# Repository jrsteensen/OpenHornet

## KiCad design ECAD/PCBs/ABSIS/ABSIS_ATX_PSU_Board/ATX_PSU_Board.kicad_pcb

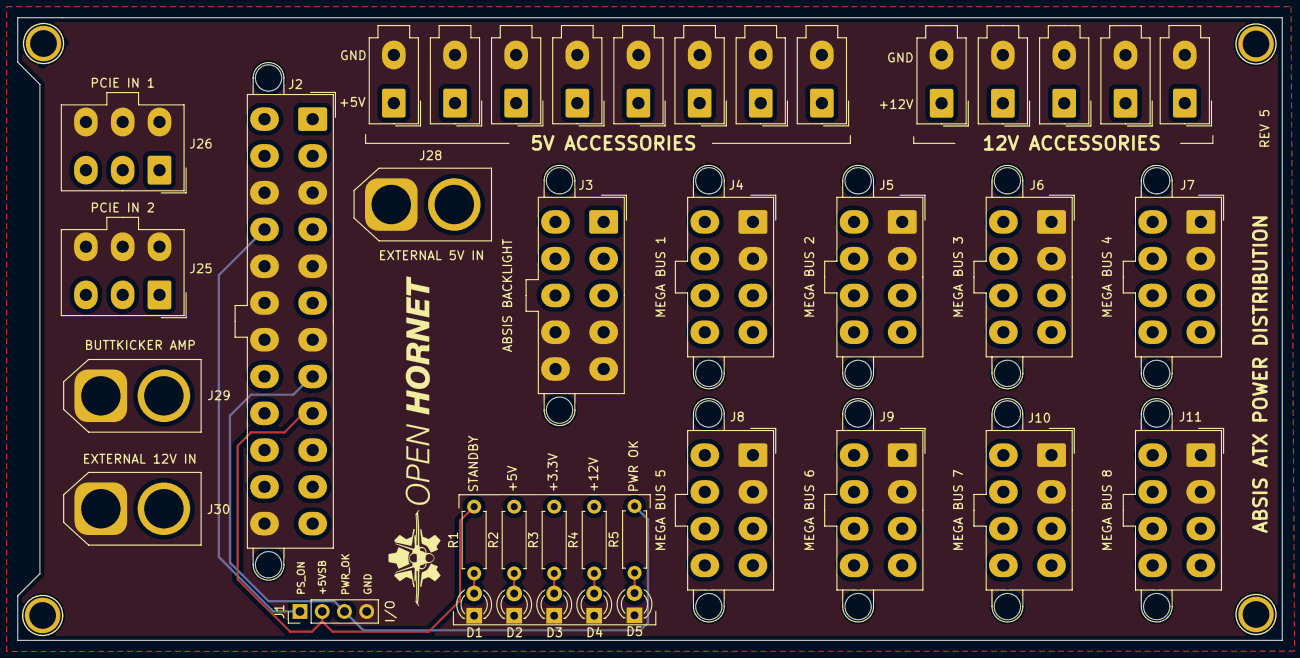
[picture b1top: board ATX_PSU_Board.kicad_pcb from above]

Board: 4 copper layers, 144.4 x 71.1 mm, 43 parts (0 on the bottom side), 12 nets.

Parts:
D1: Blue LED; LED_D3.0mm
D2, D3, D4, D5: Green LED; LED_D3.0mm
H1, H2, H3, H4: MountingHole; Arduino_1pin
J1: I/O; PinHeader_1x04_P2.54mm_Vertical
J2: ATX-24; Molex_Mini-Fit_Jr_5566-24A2_2x12_P4.20mm_Vertical
J3: ABSIS BACKLIGHT; Molex_Mini-Fit_Jr_5566-10A2_2x05_P4.20mm_Vertical
J4: MEGA BUS 1; Molex_Mini-Fit_Jr_5566-08A2_2x04_P4.20mm_Vertical
J5: MEGA BUS 2; Molex_Mini-Fit_Jr_5566-08A2_2x04_P4.20mm_Vertical
J6: MEGA BUS 3; Molex_Mini-Fit_Jr_5566-08A2_2x04_P4.20mm_Vertical
J7: MEGA BUS 4; Molex_Mini-Fit_Jr_5566-08A2_2x04_P4.20mm_Vertical
J8: MEGA BUS 5; Molex_Mini-Fit_Jr_5566-08A2_2x04_P4.20mm_Vertical
J9: MEGA BUS 6; Molex_Mini-Fit_Jr_5566-08A2_2x04_P4.20mm_Vertical
J10: MEGA BUS 7; Molex_Mini-Fit_Jr_5566-08A2_2x04_P4.20mm_Vertical
J11: MEGA BUS 8; Molex_Mini-Fit_Jr_5566-08A2_2x04_P4.20mm_Vertical
J12: 5V Accessory 1; Molex_Mini-Fit_Jr_5566-02A_2x01_P4.20mm_Vertical
J13: 5V Accessory 2; Molex_Mini-Fit_Jr_5566-02A_2x01_P4.20mm_Vertical
J14: 5V Accessory 3; Molex_Mini-Fit_Jr_5566-02A_2x01_P4.20mm_Vertical
J15: 5V Accessory 4; Molex_Mini-Fit_Jr_5566-02A_2x01_P4.20mm_Vertical
J16: 5V Accessory 5; Molex_Mini-Fit_Jr_5566-02A_2x01_P4.20mm_Vertical
J17: 5V Accessory 6; Molex_Mini-Fit_Jr_5566-02A_2x01_P4.20mm_Vertical
J18: 5V Accessory 7; Molex_Mini-Fit_Jr_5566-02A_2x01_P4.20mm_Vertical
J19: 5V Accessory 8; Molex_Mini-Fit_Jr_5566-02A_2x01_P4.20mm_Vertical
J20: 12V Accessory 1; Molex_Mini-Fit_Jr_5566-02A_2x01_P4.20mm_Vertical
J21: 12V Accessory 2; Molex_Mini-Fit_Jr_5566-02A_2x01_P4.20mm_Vertical
J22: 12V Accessory 3; Molex_Mini-Fit_Jr_5566-02A_2x01_P4.20mm_Vertical
J23: 12V Accessory 4; Molex_Mini-Fit_Jr_5566-02A_2x01_P4.20mm_Vertical
J24: 12V Accessory 5; Molex_Mini-Fit_Jr_5566-02A_2x01_P4.20mm_Vertical
J25: PCIE IN 2; Molex_Mini-Fit_Jr_5566-06A_2x03_P4.20mm_Vertical
J26: PCIE IN 1; Molex_Mini-Fit_Jr_5566-06A_2x03_P4.20mm_Vertical
J28: EXTERNAL 5V IN; AMASS_XT60-M_1x02_P7.20mm_Vertical
J29: BUTTKICKER AMP; AMASS_XT60-F_1x02_P7.20mm_Vertical
J30: EXTERNAL 12V IN; AMASS_XT60-M_1x02_P7.20mm_Vertical
R1, R2, R5: 150; R_Axial_DIN0207_L6.3mm_D2.5mm_P7.62mm_Horizontal
R3: 56; R_Axial_DIN0207_L6.3mm_D2.5mm_P7.62mm_Horizontal
R4: 560; R_Axial_DIN0207_L6.3mm_D2.5mm_P7.62mm_Horizontal

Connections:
/+3.3V_SUPPLY: J2.1, J2.2, J2.12, J2.13, J4.5, J5.5, J6.5, J7.5, J8.5, J9.5, J10.5, J11.5, R3.2
/+5VSB_SUPPLY: J1.2, J2.9, R1.2
/+5V_SUPPLY: J2.4, J2.6, J2.21, J2.22, J2.23, J3.1, J3.2, J3.3, J3.6, J3.7, J4.6, J4.7, J5.6, J5.7, J6.6, J6.7, J7.6, J7.7, J8.6, J8.7, J9.6, J9.7, J10.6, J10.7, J11.6, J11.7, J12.1, J13.1, J14.1, J15.1, J16.1, J17.1, J18.1, J19.1, J28.2, R2.2
/+12V_SUPPLY: J2.10, J2.11, J3.8, J4.3, J4.4, J4.8, J5.3, J5.4, J5.8, J6.3, J6.4, J6.8, J7.3, J7.4, J7.8, J8.3, J8.4, J8.8, J9.3, J9.4, J9.8, J10.3, J10.4, J10.8, J11.3, J11.4, J11.8, J20.1, J21.1, J22.1, J23.1, J24.1, J25.1, J25.2, J25.3, J26.1, J26.2, J26.3, J29.2, J30.2, R4.2
/PS_ON: J1.1, J2.16
/PWR_OK: J1.3, J2.8, R5.2
GND: D1.1, D2.1, D3.1, D4.1, D5.1, J1.4, J2.3, J2.5, J2.7, J2.15, J2.17, J2.18, J2.19, J2.24, J3.4, J3.5, J3.9, J3.10, J4.1, J4.2, J5.1, J5.2, J6.1, J6.2, J7.1, J7.2, J8.1, J8.2, J9.1, J9.2, J10.1, J10.2, J11.1, J11.2, J12.2, J13.2, J14.2, J15.2, J16.2, J17.2, J18.2, J19.2, J20.2, J21.2, J22.2, J23.2, J24.2, J25.4, J25.5, J25.6, J26.4, J26.5, J26.6, J28.1, J29.1, J30.1
unnamed: D1.2, R1.1
unnamed: D2.2, R2.1
unnamed: D3.2, R3.1
unnamed: D4.2, R4.1
unnamed: D5.2, R5.1

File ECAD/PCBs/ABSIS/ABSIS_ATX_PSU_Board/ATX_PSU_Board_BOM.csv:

"Id";"Designator";"Package";"Quantity";"Designation";"Supplier and ref";
1;"R4";"R_0603_1608Metric_Pad0.98x0.95mm_HandSolder";1;"560";;;
2;"R3";"R_0603_1608Metric_Pad0.98x0.95mm_HandSolder";1;"56";;;
3;"R2,R1";"R_0603_1608Metric_Pad0.98x0.95mm_HandSolder";2;"150";;;
4;"D4,D3,D2,D1";"LED_0603_1608Metric_Pad1.05x0.95mm_HandSolder";4;"Green LED";;;
5;"J1";"PinHeader_1x02_P2.54mm_Vertical";1;"Power Swtich";;;
6;"G***,G***";"CC-BY-NC-SA-Small";2;"LOGO";;;
7;"G***";"OH_LOGO_75.4mm_11.9mm";1;"LOGO";;;
8;"J5,J10,J9,J8,J7,J6,J4";"Molex_Mini-Fit_Jr_5566-08A2_2x04_P4.20mm_Vertical";7;"MEGA BUS POWER";;;
9;"G***";"OH_LOGO_37.7mm_5.9mm";1;"LOGO";;;
10;"H4,H3,H2,H1";"Arduino_1pin";4;"MountingHole";;;
11;"J3";"Molex_Mini-Fit_Jr_5566-10A2_2x05_P4.20mm_Vertical";1;"ABSIS BACKLIGHT PWR";;;
12;"J2";"Molex_Mini-Fit_Jr_5566-24A2_2x12_P4.20mm_Vertical";1;"ATX-24";;;

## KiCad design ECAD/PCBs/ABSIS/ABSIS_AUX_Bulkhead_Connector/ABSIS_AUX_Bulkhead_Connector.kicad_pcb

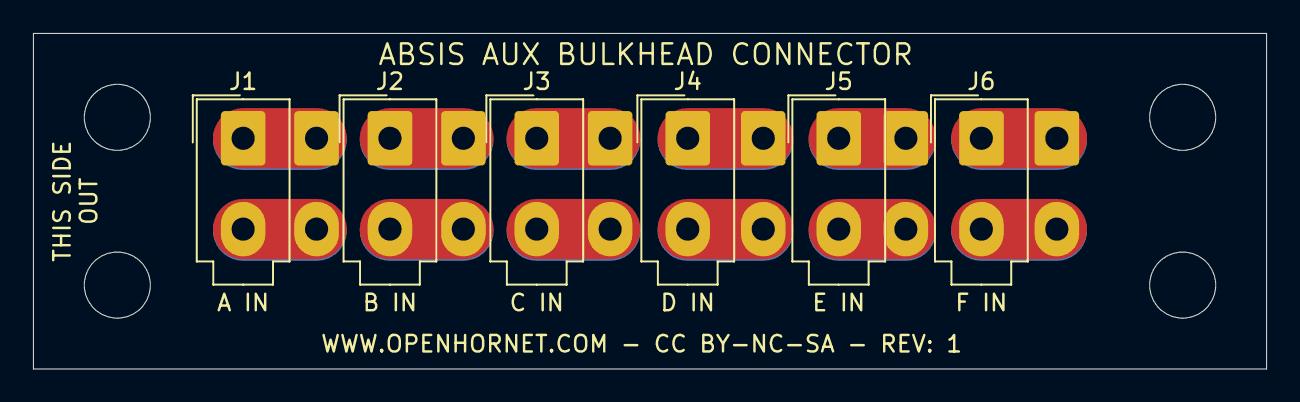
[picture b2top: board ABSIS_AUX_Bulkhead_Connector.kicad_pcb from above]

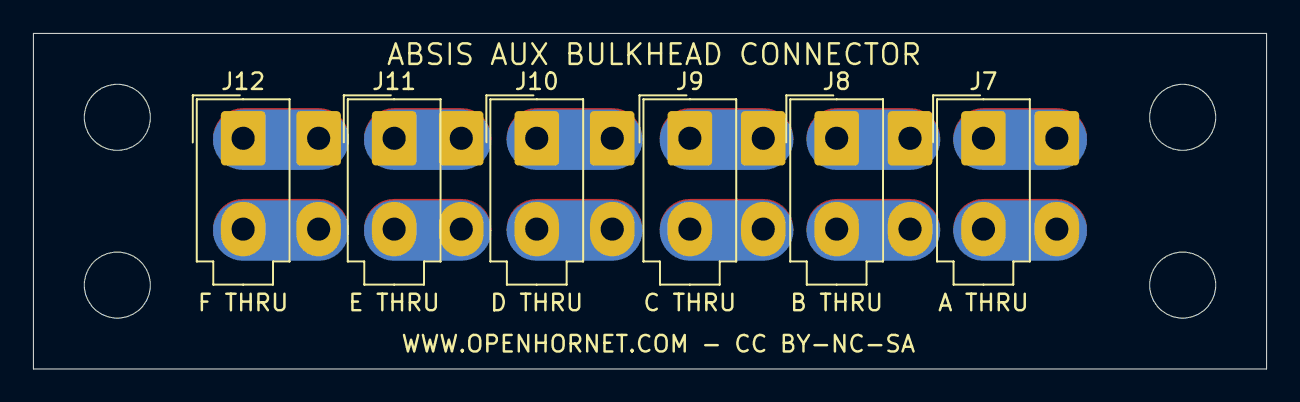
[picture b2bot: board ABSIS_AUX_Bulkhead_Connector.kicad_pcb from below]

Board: 2 copper layers, 74.7 x 20.3 mm, 16 parts (6 on the bottom side), 12 nets.

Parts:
H1, H2, H3, H4: MH; MountingHole_4mm
J1: A IN; Molex_Mini-Fit_Jr_5566-02A_2x01_P4.20mm_Vertical
J2: B IN; Molex_Mini-Fit_Jr_5566-02A_2x01_P4.20mm_Vertical
J3: C IN; Molex_Mini-Fit_Jr_5566-02A_2x01_P4.20mm_Vertical
J4: D IN; Molex_Mini-Fit_Jr_5566-02A_2x01_P4.20mm_Vertical
J5: E IN; Molex_Mini-Fit_Jr_5566-02A_2x01_P4.20mm_Vertical
J6: F IN; Molex_Mini-Fit_Jr_5566-02A_2x01_P4.20mm_Vertical
J7: A THRU; Molex_Mini-Fit_Jr_5566-02A_2x01_P4.20mm_Vertical
J8: B THRU; Molex_Mini-Fit_Jr_5566-02A_2x01_P4.20mm_Vertical
J9: C THRU; Molex_Mini-Fit_Jr_5566-02A_2x01_P4.20mm_Vertical
J10: D THRU; Molex_Mini-Fit_Jr_5566-02A_2x01_P4.20mm_Vertical
J11: E THRU; Molex_Mini-Fit_Jr_5566-02A_2x01_P4.20mm_Vertical
J12: F THRU; Molex_Mini-Fit_Jr_5566-02A_2x01_P4.20mm_Vertical

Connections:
/A1: J1.1, J7.1
/A2: J1.2, J7.2
/B1: J2.1, J8.1
/B2: J2.2, J8.2
/C1: J3.1, J9.1
/C2: J3.2, J9.2
/D1: J4.1, J10.1
/D2: J4.2, J10.2
/E1: J5.1, J11.1
/E2: J5.2, J11.2
/F1: J6.1, J12.1
/F2: J6.2, J12.2

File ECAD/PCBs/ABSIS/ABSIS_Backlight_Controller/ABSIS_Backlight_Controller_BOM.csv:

Reference, Quantity, Value, Footprint, Datasheet, PN
J1 ,1,"Molex Mini-Fit Jr, Header, 2x5",Connector_Molex:Molex_Mini-Fit_Jr_5566-10A2_2x05_P4.20mm_Vertical,https://www.molex.com/pdm_docs/sd/039299103_sd.pdf,39299103
J2 J3 J4 J5 J6 J7 J8 J9 J10 J11 J12 J13,12,"Molex Mini-Fit Jr, Header, 2x2",Connector_Molex:Molex_Mini-Fit_Jr_5566-04A_2x02_P4.20mm_Vertical,https://www.molex.com/pdm_docs/sd/039281043_sd.pdf,39281043
J14 ,1,"Pin Header, 2.54mm, 2x6",Connector_PinHeader_2.54mm:PinHeader_2x06_P2.54mm_Vertical,~,
J15 ,1,"Pin Header, 2.54mm, 2x8",Connector_PinHeader_2.54mm:PinHeader_2x08_P2.54mm_Vertical,~,
P1 ,1,Digital,Connector_PinHeader_2.54mm:PinHeader_2x18_P2.54mm_Vertical,~,
P2 P3 P4 P6 P7,5,"Pin Header, 2.54mm, 1x8",Connector_PinHeader_2.54mm:PinHeader_1x08_P2.54mm_Vertical,~,
P5 ,1,PWM,Connector_PinHeader_2.54mm:PinHeader_1x10_P2.54mm_Vertical,~,

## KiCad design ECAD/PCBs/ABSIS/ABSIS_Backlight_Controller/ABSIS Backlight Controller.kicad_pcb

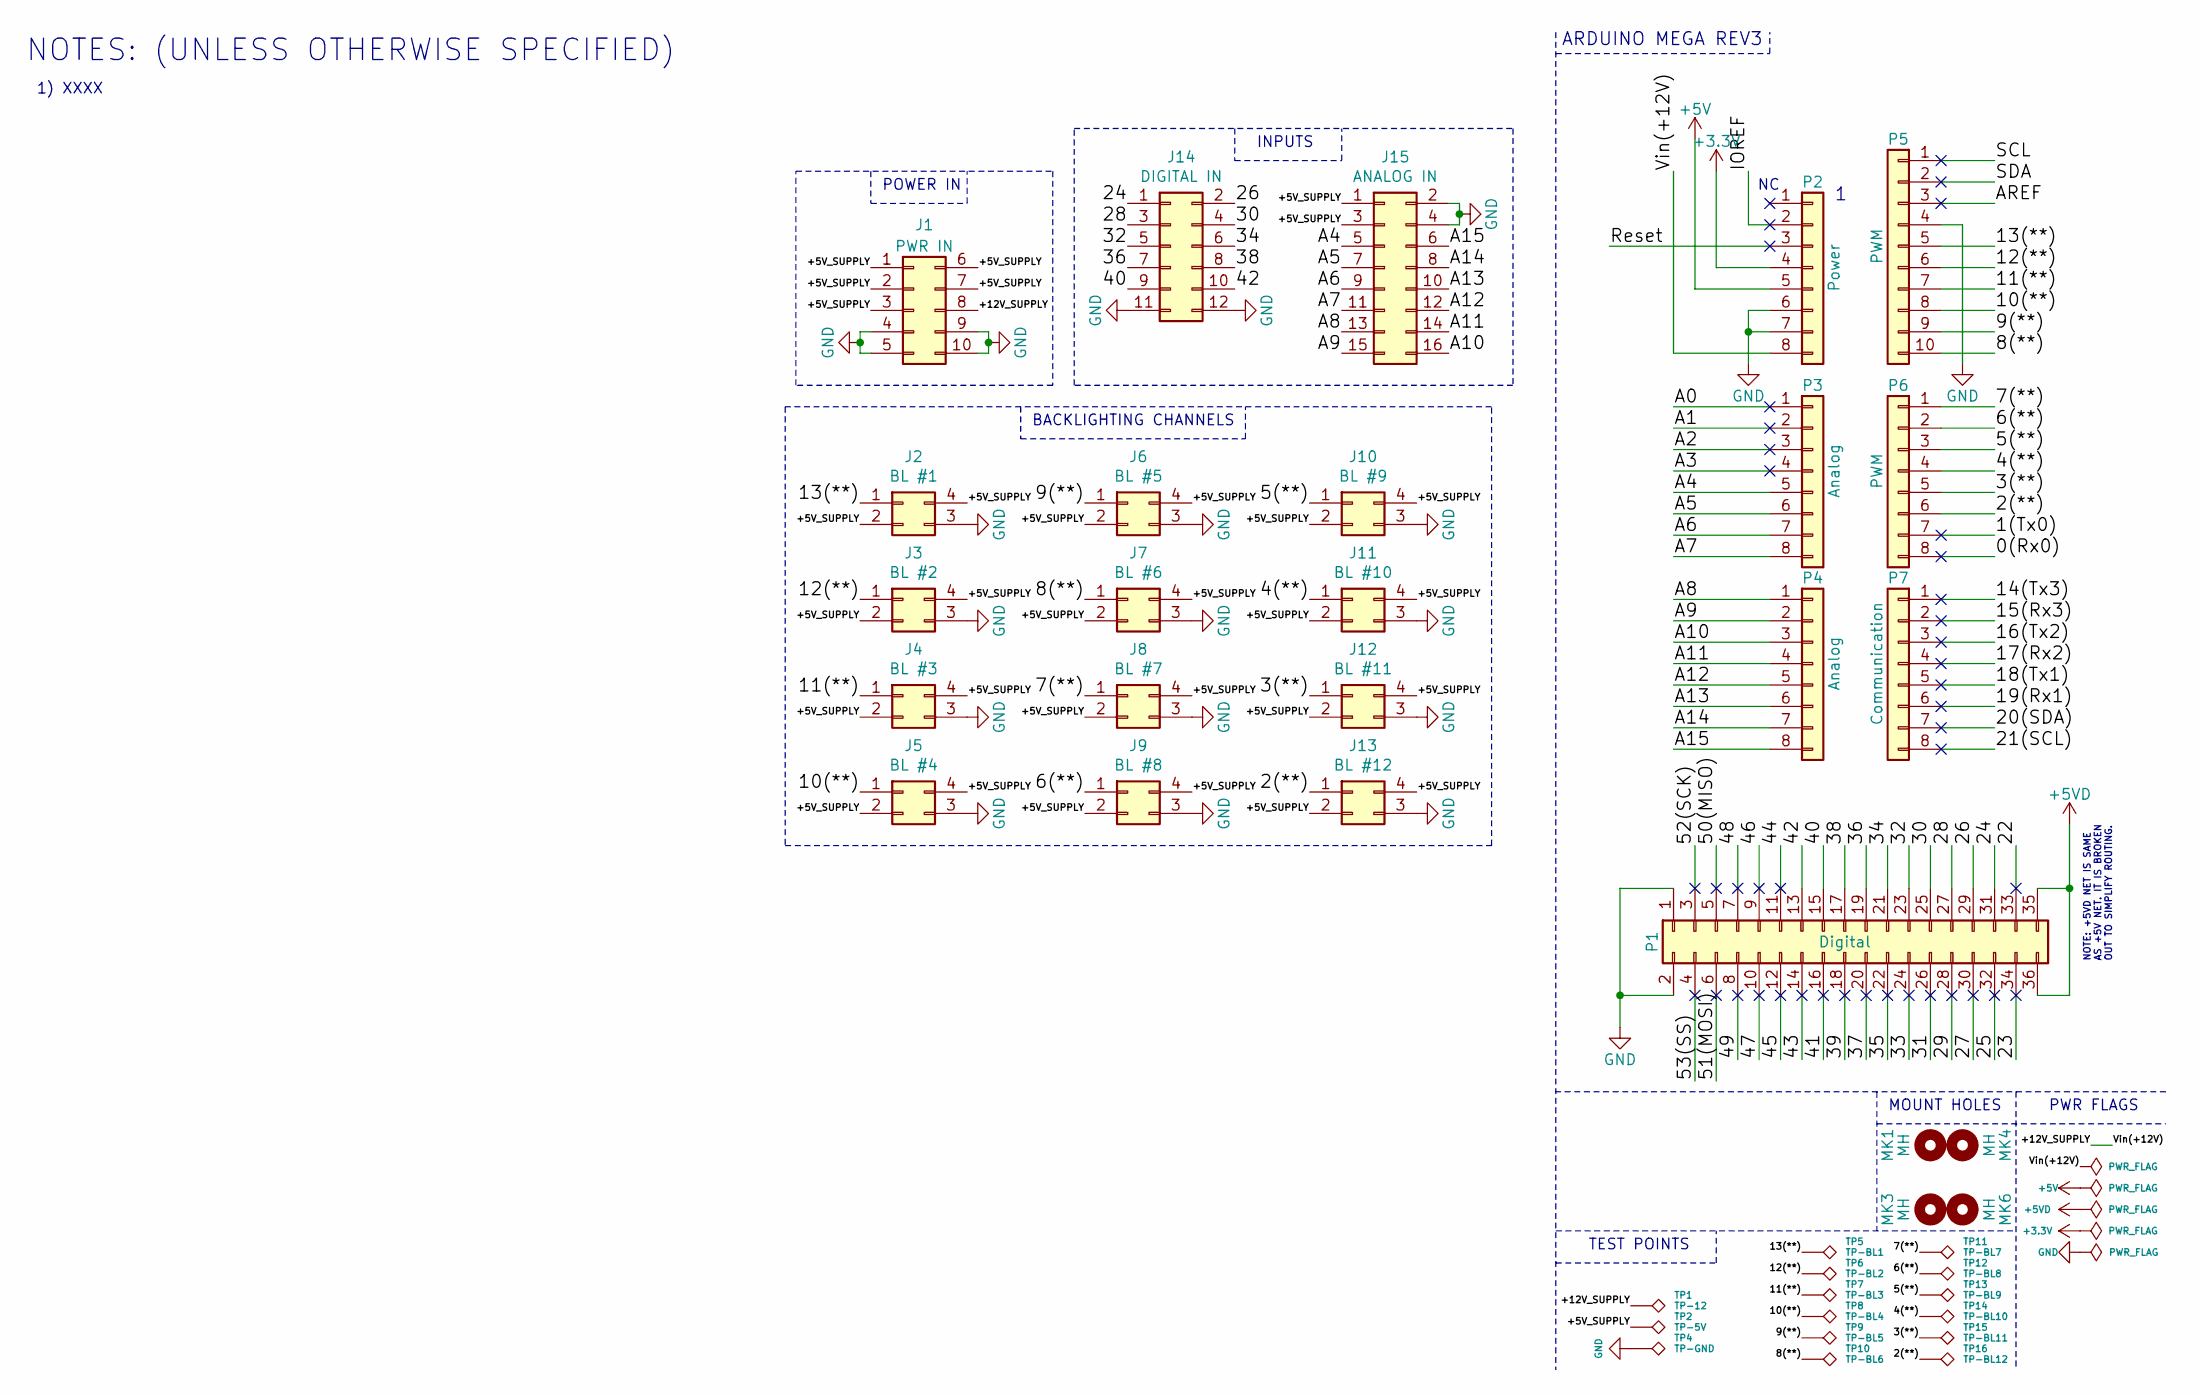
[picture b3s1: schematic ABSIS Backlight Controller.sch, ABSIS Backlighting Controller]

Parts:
J1: PWR IN; Molex_Mini-Fit_Jr_5566-10A2_2x05_P4.20mm_Vertical
J2: BL #1; Molex_Micro-Fit_3.0_43045-0412_2x02_P3.00mm_Vertical
J3: BL #2; Molex_Micro-Fit_3.0_43045-0412_2x02_P3.00mm_Vertical
J4: BL #3; Molex_Micro-Fit_3.0_43045-0412_2x02_P3.00mm_Vertical
J5: BL #4; Molex_Micro-Fit_3.0_43045-0412_2x02_P3.00mm_Vertical
J6: BL #5; Molex_Micro-Fit_3.0_43045-0412_2x02_P3.00mm_Vertical
J7: BL #6; Molex_Micro-Fit_3.0_43045-0412_2x02_P3.00mm_Vertical
J8: BL #7; Molex_Micro-Fit_3.0_43045-0412_2x02_P3.00mm_Vertical
J9: BL #8; Molex_Micro-Fit_3.0_43045-0412_2x02_P3.00mm_Vertical
J10: BL #9; Molex_Micro-Fit_3.0_43045-0412_2x02_P3.00mm_Vertical
J11: BL #10; Molex_Micro-Fit_3.0_43045-0412_2x02_P3.00mm_Vertical
J12: BL #11; Molex_Micro-Fit_3.0_43045-0412_2x02_P3.00mm_Vertical
J13: BL #12; Molex_Micro-Fit_3.0_43045-0412_2x02_P3.00mm_Vertical
J14: DIGITAL IN; PinHeader_2x06_P2.54mm_Vertical
J15: ANALOG IN; PinHeader_2x08_P2.54mm_Vertical
MK1, MK3, MK4, MK6: MH; Arduino_1pin
P1: Digital; PinHeader_2x18_P2.54mm_Vertical
P2: Power; PinHeader_1x08_P2.54mm_Vertical
P3, P4: Analog; PinHeader_1x08_P2.54mm_Vertical
P5: PWM; PinHeader_1x10_P2.54mm_Vertical
P6: PWM; PinHeader_1x08_P2.54mm_Vertical
P7: Communication; PinHeader_1x08_P2.54mm_Vertical
TP1: TP-12; TestPoint_THTPad_D1.5mm_Drill0.7mm
TP2: TP-5V; TestPoint_THTPad_D1.5mm_Drill0.7mm
TP4: TP-GND; TestPoint_THTPad_D1.5mm_Drill0.7mm
TP5: TP-BL1; TestPoint_THTPad_D1.5mm_Drill0.7mm
TP6: TP-BL2; TestPoint_THTPad_D1.5mm_Drill0.7mm
TP7: TP-BL3; TestPoint_THTPad_D1.5mm_Drill0.7mm
TP8: TP-BL4; TestPoint_THTPad_D1.5mm_Drill0.7mm
TP9: TP-BL5; TestPoint_THTPad_D1.5mm_Drill0.7mm
TP10: TP-BL6; TestPoint_THTPad_D1.5mm_Drill0.7mm
TP11: TP-BL7; TestPoint_THTPad_D1.5mm_Drill0.7mm
TP12: TP-BL8; TestPoint_THTPad_D1.5mm_Drill0.7mm
TP13: TP-BL9; TestPoint_THTPad_D1.5mm_Drill0.7mm
TP14: TP-BL10; TestPoint_THTPad_D1.5mm_Drill0.7mm
TP15: TP-BL11; TestPoint_THTPad_D1.5mm_Drill0.7mm
TP16: TP-BL12; TestPoint_THTPad_D1.5mm_Drill0.7mm

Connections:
+3V3: P2.4
+5V: P2.5
+5VD: P1.35, P1.36
/0(Rx0): P6.8
/1(Tx0): P6.7
/2(**): J13.1, P6.6, TP16.1
/3(**): J12.1, P6.5, TP15.1
/4(**): J11.1, P6.4, TP14.1
/5(**): J10.1, P6.3, TP13.1
/6(**): J9.1, P6.2, TP12.1
/7(**): J8.1, P6.1, TP11.1
/8(**): J7.1, P5.10, TP10.1
/9(**): J6.1, P5.9, TP9.1
/10(**): J5.1, P5.8, TP8.1
/11(**): J4.1, P5.7, TP7.1
/12(**): J3.1, P5.6, TP6.1
/13(**): J2.1, P5.5, TP5.1
/14(Tx3): P7.1
/15(Rx3): P7.2
/16(Tx2): P7.3
/17(Rx2): P7.4
/18(Tx1): P7.5
/19(Rx1): P7.6
/20(SDA): P7.7
/21(SCL): P7.8
/22: P1.33
/23: P1.34
/24: J14.1, P1.31
/25: P1.32
/26: J14.2, P1.29
/27: P1.30
/28: J14.3, P1.27
/29: P1.28
/30: J14.4, P1.25
/31: P1.26
/32: J14.5, P1.23
/33: P1.24
/34: J14.6, P1.21
/35: P1.22
/36: J14.7, P1.19
/37: P1.20
/38: J14.8, P1.17
/39: P1.18
/40: J14.9, P1.15
/41: P1.16
/42: J14.10, P1.13
/43: P1.14
/44: P1.11
/45: P1.12
/46: P1.9
/47: P1.10
/48: P1.7
/49: P1.8
/50(MISO): P1.5
/51(MOSI): P1.6
/52(SCK): P1.3
/53(SS): P1.4
/+5V_SUPPLY: J1.1, J1.2, J1.3, J1.6, J1.7, J2.2, J2.4, J3.2, J3.4, J4.2, J4.4, J5.2, J5.4, J6.2, J6.4, J7.2, J7.4, J8.2, J8.4, J9.2, J9.4, J10.2, J10.4, J11.2, J11.4, J12.2, J12.4, J13.2, J13.4, J15.1, J15.3, TP2.1
/+12V_SUPPLY: J1.8, P2.8, TP1.1
/A0: P3.1
/A1: P3.2
/A2: P3.3
/A3: P3.4
/A4: J15.5, P3.5
/A5: J15.7, P3.6
/A6: J15.9, P3.7
/A7: J15.11, P3.8
/A8: J15.13, P4.1
/A9: J15.15, P4.2
/A10: J15.16, P4.3
/A11: J15.14, P4.4
/A12: J15.12, P4.5
/A13: J15.10, P4.6
/A14: J15.8, P4.7
/A15: J15.6, P4.8
/AREF: P5.3
/IOREF: P2.2
/Reset: P2.3
/SCL: P5.1
/SDA: P5.2
GND: J1.4, J1.5, J1.9, J1.10, J2.3, J3.3, J4.3, J5.3, J6.3, J7.3, J8.3, J9.3, J10.3, J11.3, J12.3, J13.3, J14.11, J14.12, J15.2, J15.4, P1.1, P1.2, P2.6, P2.7, P5.4, TP4.1

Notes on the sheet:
ARDUINO MEGA REV3
NOTES: (UNLESS OTHERWISE SPECIFIED)
1) XXXX
MOUNT HOLES
NOTE: +5VD NET IS SAME AS +5V NET. IT IS BROKEN OUT TO SIMPLIFY ROUTING.
PWR FLAGS
TEST POINTS
BACKLIGHTING CHANNELS
INPUTS
POWER IN

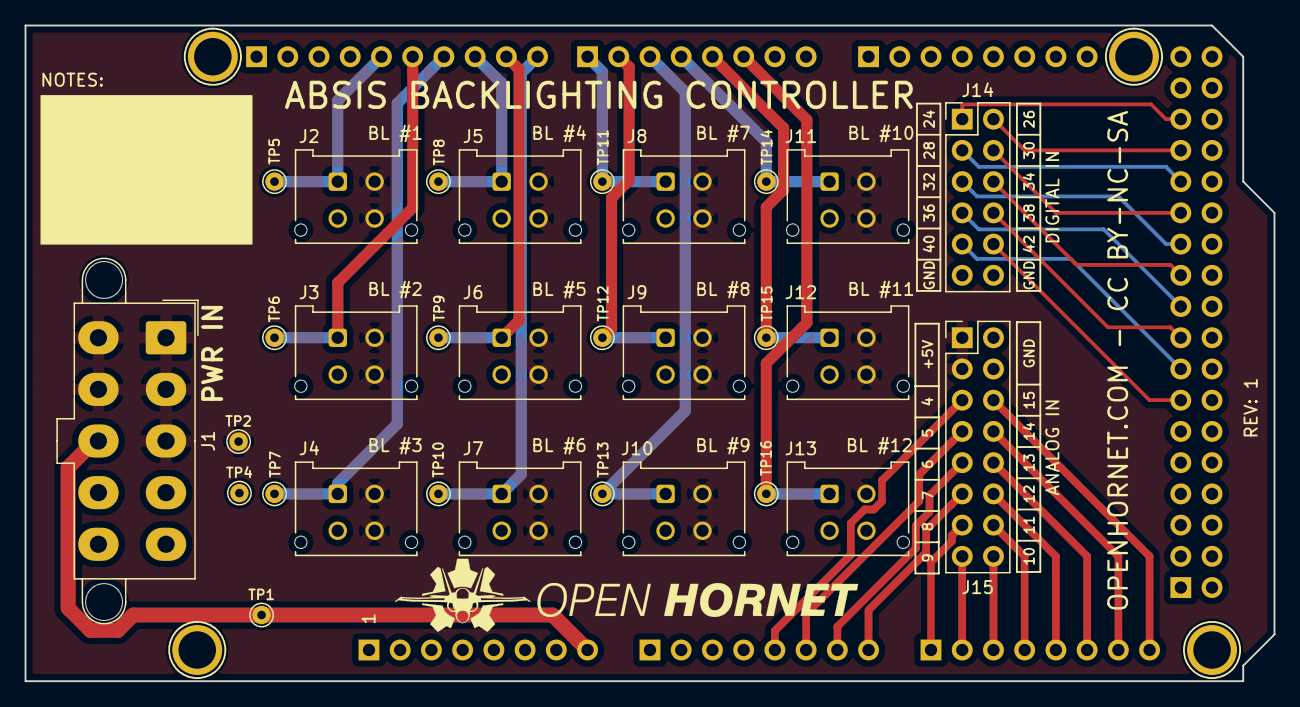
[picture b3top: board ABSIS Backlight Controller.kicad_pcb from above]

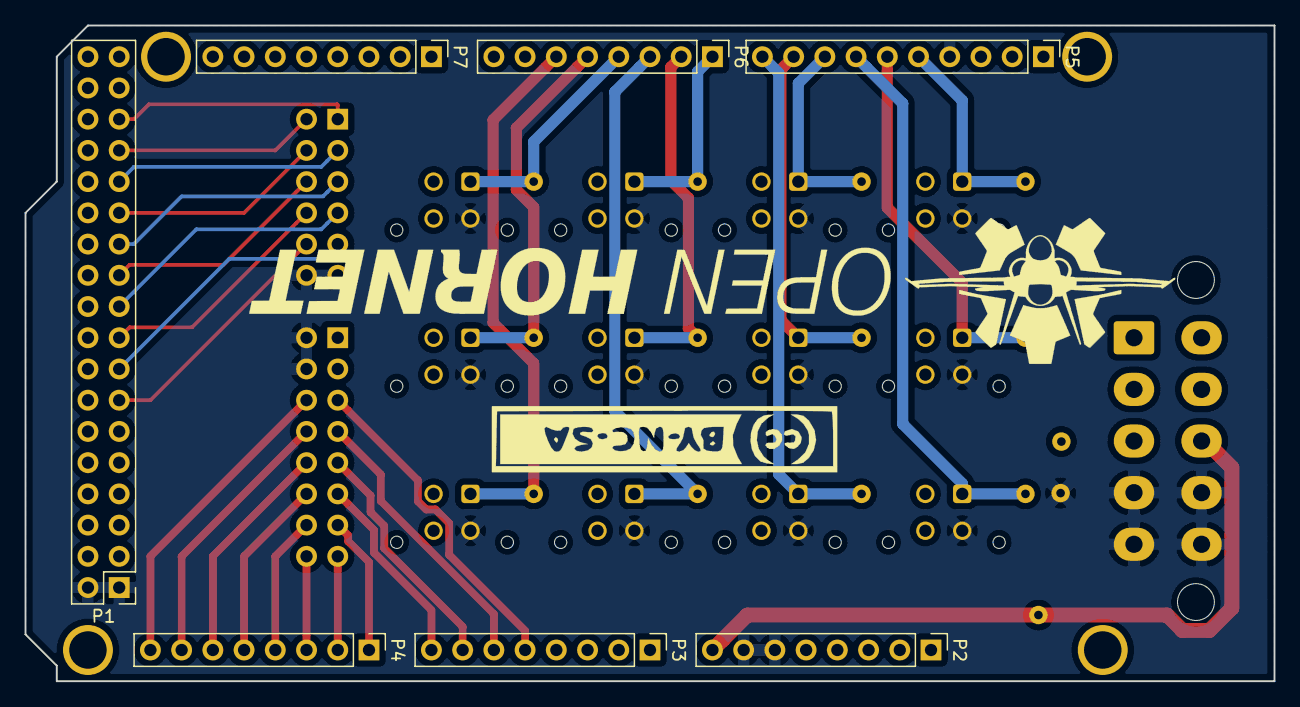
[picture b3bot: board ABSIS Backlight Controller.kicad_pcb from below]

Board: 2 copper layers, 101.6 x 53.3 mm, 41 parts (7 on the bottom side), 38 nets.

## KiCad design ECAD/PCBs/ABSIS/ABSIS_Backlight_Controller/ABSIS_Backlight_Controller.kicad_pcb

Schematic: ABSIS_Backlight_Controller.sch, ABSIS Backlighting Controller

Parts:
D1: 5V; LED_0603_1608Metric_Pad1.05x0.95mm_HandSolder
D2: 12V; LED_0603_1608Metric_Pad1.05x0.95mm_HandSolder
J1: PWR IN; Molex_Mini-Fit_Jr_5566-10A2_2x05_P4.20mm_Vertical
J2: BL #1; Molex_Mini-Fit_Jr_5566-04A_2x02_P4.20mm_Vertical
J3: BL #2; Molex_Mini-Fit_Jr_5566-04A_2x02_P4.20mm_Vertical
J4: BL #3; Molex_Mini-Fit_Jr_5566-04A_2x02_P4.20mm_Vertical
J5: BL #4; Molex_Mini-Fit_Jr_5566-04A_2x02_P4.20mm_Vertical
J6: BL #5; Molex_Mini-Fit_Jr_5566-04A_2x02_P4.20mm_Vertical
J7: BL #6; Molex_Mini-Fit_Jr_5566-04A_2x02_P4.20mm_Vertical
J8: BL #7; Molex_Mini-Fit_Jr_5566-04A_2x02_P4.20mm_Vertical
J9: BL #8; Molex_Mini-Fit_Jr_5566-04A_2x02_P4.20mm_Vertical
J10: BL #9; Molex_Mini-Fit_Jr_5566-04A_2x02_P4.20mm_Vertical
J11: BL #10; Molex_Mini-Fit_Jr_5566-04A_2x02_P4.20mm_Vertical
J12, J13: Conn_01x04_Female; Molex_KK-254_AE-6410-04A_1x04_P2.54mm_Vertical
J16: Fan voltage selector; PinHeader_1x03_P2.54mm_Vertical
MK1, MK3, MK4, MK6: MH; Arduino_1pin
P1: Digital; PinHeader_2x18_P2.54mm_Vertical
P2: Power; PinHeader_1x08_P2.54mm_Vertical
P3, P4: Analog; PinHeader_1x08_P2.54mm_Vertical
P5: PWM; PinHeader_1x10_P2.54mm_Vertical
P6: PWM; PinHeader_1x08_P2.54mm_Vertical
P7: Communication; PinHeader_1x08_P2.54mm_Vertical
R1: 470; R_0603_1608Metric_Pad1.05x0.95mm_HandSolder
R2: 1K; R_0603_1608Metric_Pad1.05x0.95mm_HandSolder
TP1: TP-12; TestPoint_THTPad_D1.5mm_Drill0.7mm
TP2: TP-5V; TestPoint_THTPad_D1.5mm_Drill0.7mm
TP4: TP-GND; TestPoint_THTPad_D1.5mm_Drill0.7mm
TP5: TP-BL1; TestPoint_THTPad_D1.5mm_Drill0.7mm
TP6: TP-BL2; TestPoint_THTPad_D1.5mm_Drill0.7mm
TP7: TP-BL3; TestPoint_THTPad_D1.5mm_Drill0.7mm
TP8: TP-BL4; TestPoint_THTPad_D1.5mm_Drill0.7mm
TP9: TP-BL5; TestPoint_THTPad_D1.5mm_Drill0.7mm
TP10: TP-BL6; TestPoint_THTPad_D1.5mm_Drill0.7mm
TP11: TP-BL7; TestPoint_THTPad_D1.5mm_Drill0.7mm
TP12: TP-BL8; TestPoint_THTPad_D1.5mm_Drill0.7mm
TP13: TP-BL9; TestPoint_THTPad_D1.5mm_Drill0.7mm
TP14: TP-BL10; TestPoint_THTPad_D1.5mm_Drill0.7mm
U1: LM75C; SOIC-8_3.9x4.9mm_P1.27mm

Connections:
+3V3: P2.4
+5V: P2.5
+5VD: P1.35, P1.36
/0(Rx0): P6.8
/1(Tx0): P6.7
/2(**): J12.4, J13.4, P6.6
/3(**): P6.5; also elsewhere on the board
/4(**): J11.4, P6.4, TP14.1
/5(**): J10.4, P6.3, TP13.1
/6(**): J9.4, P6.2, TP12.1
/7(**): J8.4, P6.1, TP11.1
/8(**): J7.4, P5.10, TP10.1
/9(**): J6.4, P5.9, TP9.1
/10(**): J5.4, P5.8, TP8.1
/11(**): J4.4, P5.7, TP7.1
/12(**): J3.4, P5.6, TP6.1
/13(**): J2.4, P5.5, TP5.1
/14(Tx3): P7.1
/15(Rx3): P7.2
/16(Tx2): P7.3
/17(Rx2): P7.4
/18(Tx1): P7.5
/19(Rx1): P7.6
/20(SDA): P7.7
/21(SCL): P7.8
/22: P1.33; also elsewhere on the board
/23: P1.34; also elsewhere on the board
/24: P1.31; also elsewhere on the board
/25: P1.32
/26: P1.29
/27: P1.30
/28: P1.27
/29: P1.28
/30: P1.25
/31: P1.26
/32: P1.23
/33: P1.24
/34: P1.21
/35: P1.22
/36: P1.19
/37: P1.20
/38: P1.17
/39: P1.18
/40: P1.15
/41: P1.16
/42: P1.13
/43: P1.14
/44: P1.11
/45: P1.12
/46: P1.9
/47: P1.10
/48: P1.7
/49: P1.8
/50(MISO): P1.5
/51(MOSI): P1.6
/52(SCK): P1.3
/53(SS): P1.4
/+5V_SUPPLY: D1.2, J1.1, J1.2, J1.3, J1.6, J1.7, J2.1, J2.2, J3.1, J3.2, J4.1, J4.2, J5.1, J5.2, J6.1, J6.2, J7.1, J7.2, J8.1, J8.2, J9.1, J9.2, J10.1, J10.2, J11.1, J11.2, J16.1, TP2.1, U1.8; also elsewhere on the board
/+12V_SUPPLY: D2.2, J1.8, J16.3, P2.8, TP1.1
/A0: P3.1
/A1: P3.2
/A2: P3.3
/A3: P3.4
/A4: P3.5
/A5: P3.6
/A6: P3.7
/A7: P3.8
/A8: P4.1
/A9: P4.2
/A10: P4.3
/A11: P4.4
/A12: P4.5
/A13: P4.6
/A14: P4.7
/A15: P4.8
/AREF: P5.3
/FAN_SUPPLY: J12.2, J13.2, J16.2
/IOREF: P2.2
/Reset: P2.3
/SCL: P5.1, U1.2
/SDA: P5.2, U1.1
GND: J1.4, J1.5, J1.9, J1.10, J2.3, J3.3, J4.3, J5.3, J6.3, J7.3, J8.3, J9.3, J10.3, J11.3, J12.1, J13.1, P1.1, P1.2, P2.6, P2.7, P5.4, R1.1, R2.1, TP4.1, U1.4; also elsewhere on the board
unnamed: D1.1, R1.2
unnamed: D2.1, R2.2

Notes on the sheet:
ARDUINO MEGA REV3
NOTES: (UNLESS OTHERWISE SPECIFIED)
1) XXXX
MOUNT HOLES
PWR FLAGS
TEST POINTS
BACKLIGHTING CHANNELS
POWER IN
TOP ROW
BOTTOM ROW
NOTE: +5VD NET IS SAME AS +5V NET. IT IS BROKEN OUT TO SIMPLIFY ROUTING.
READY LEDS
FAN VOLTAGE SELECTOR
COOLING FANS
TEMP SENSOR

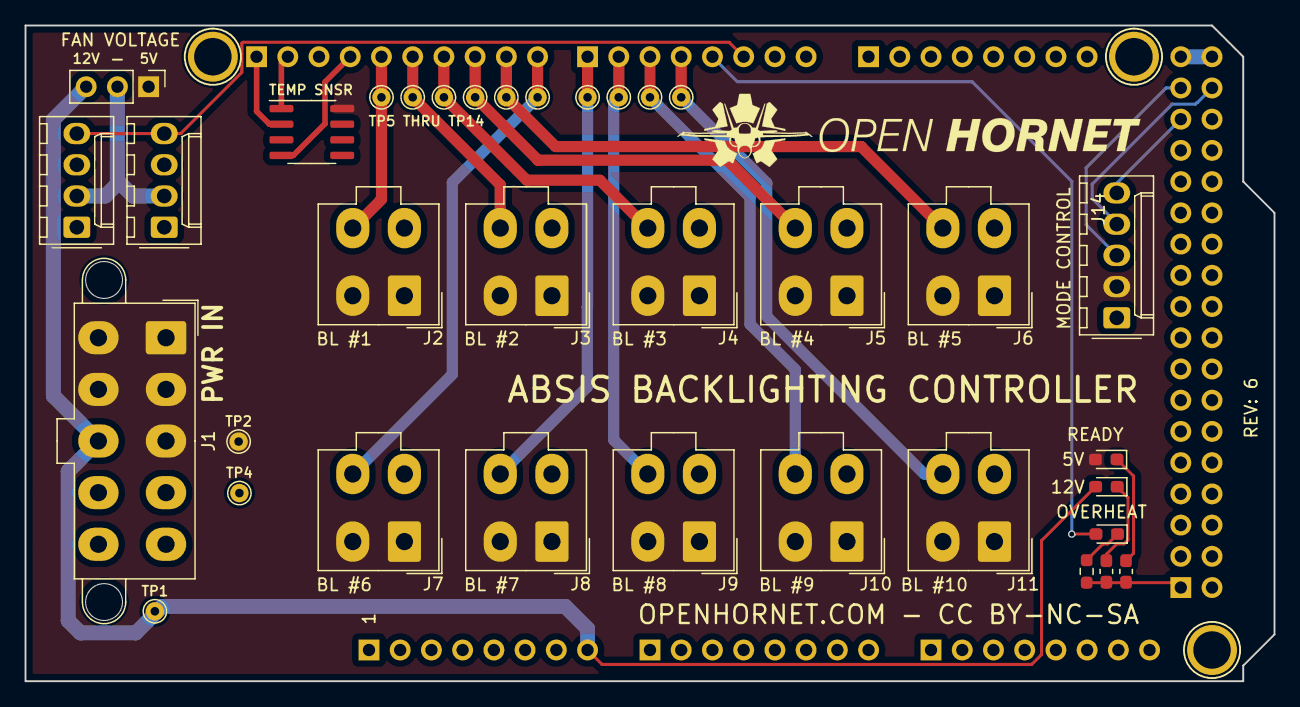
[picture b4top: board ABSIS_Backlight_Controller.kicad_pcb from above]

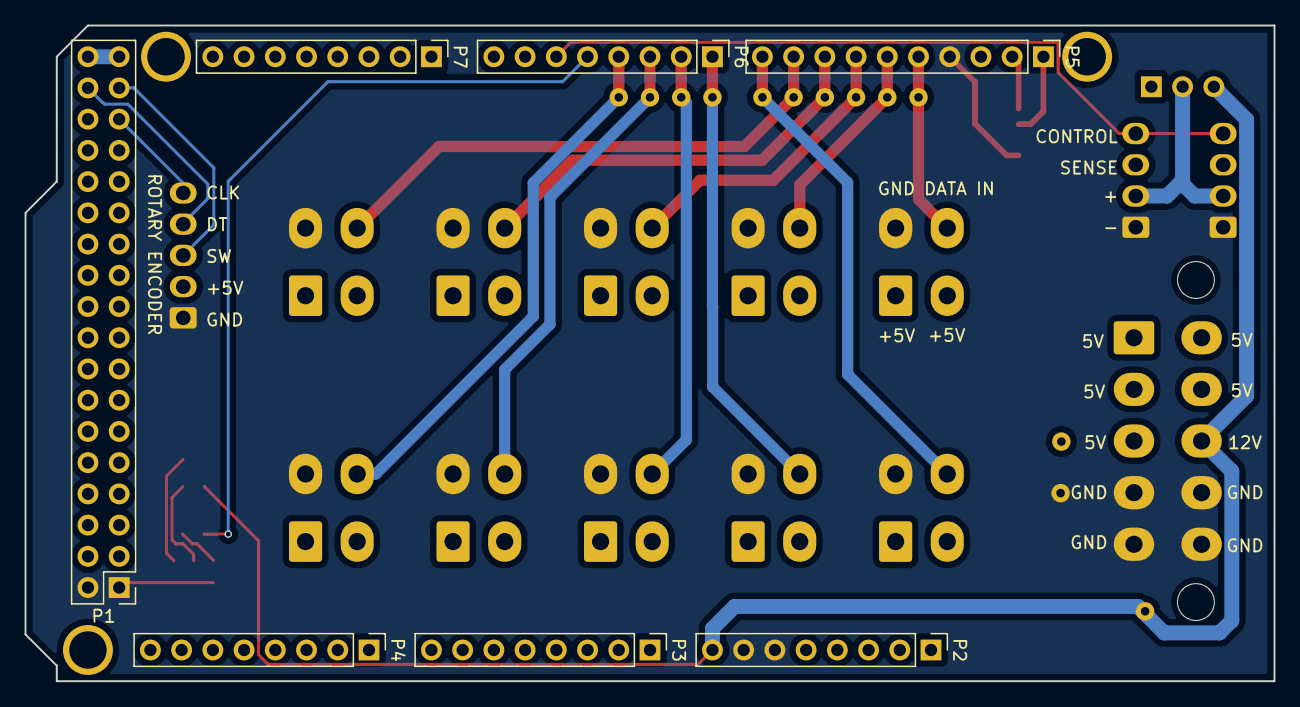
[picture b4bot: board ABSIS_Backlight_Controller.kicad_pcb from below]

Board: 2 copper layers, 101.6 x 53.3 mm, 45 parts (7 on the bottom side), 25 nets.

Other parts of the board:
D3: Overtemp; LED_0603_1608Metric_Pad1.05x0.95mm_HandSolder
J14: Conn_01x05_Female; Molex_KK-254_AE-6410-05A_1x05_P2.54mm_Vertical
R3: 2.2K; R_0603_1608Metric_Pad0.98x0.95mm_HandSolder

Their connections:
/3(**): D3.2; also elsewhere on the board
/22: J14.3; also elsewhere on the board
/23: J14.4; also elsewhere on the board
/24: J14.5; also elsewhere on the board
/+5V_SUPPLY: J14.2; also elsewhere on the board
GND: J14.1, R3.1; also elsewhere on the board
unnamed: D3.1, R3.2

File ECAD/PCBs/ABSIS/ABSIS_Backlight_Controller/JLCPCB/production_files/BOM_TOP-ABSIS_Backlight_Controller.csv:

Comment,Designator,Footprint,LCSC
Overtemp,D3,LED_0603_1608Metric_Pad1.05x0.95mm_HandSolder,C2286
4.7K,R2,R_0603_1608Metric_Pad1.05x0.95mm_HandSolder,C23162
2.2K,"R1,R3",R_0603_1608Metric_Pad1.05x0.95mm_HandSolder,C23179
BL #9,"J10,J11,J2,J3,J4,J5,J6,J7,J8,J9",Molex_Mini-Fit_Jr_5566-04A_2x02_P4.20mm_Vertical,C293502
Conn_01x04_Female,"J12,J13",Molex_KK-254_AE-6410-04A_1x04_P2.54mm_Vertical,C504991
Conn_01x05_Female,J14,Molex_KK-254_AE-6410-05A_1x05_P2.54mm_Vertical,C585785
PWR IN,J1,Molex_Mini-Fit_Jr_5566-10A2_2x05_P4.20mm_Vertical,C587474
5V,"D1,D2",LED_0603_1608Metric_Pad1.05x0.95mm_HandSolder,C72043
LM75C,U1,SOIC-8_3.9x4.9mm_P1.27mm,C7963
Fan voltage selector,J16,PinHeader_1x03_P2.54mm_Vertical,

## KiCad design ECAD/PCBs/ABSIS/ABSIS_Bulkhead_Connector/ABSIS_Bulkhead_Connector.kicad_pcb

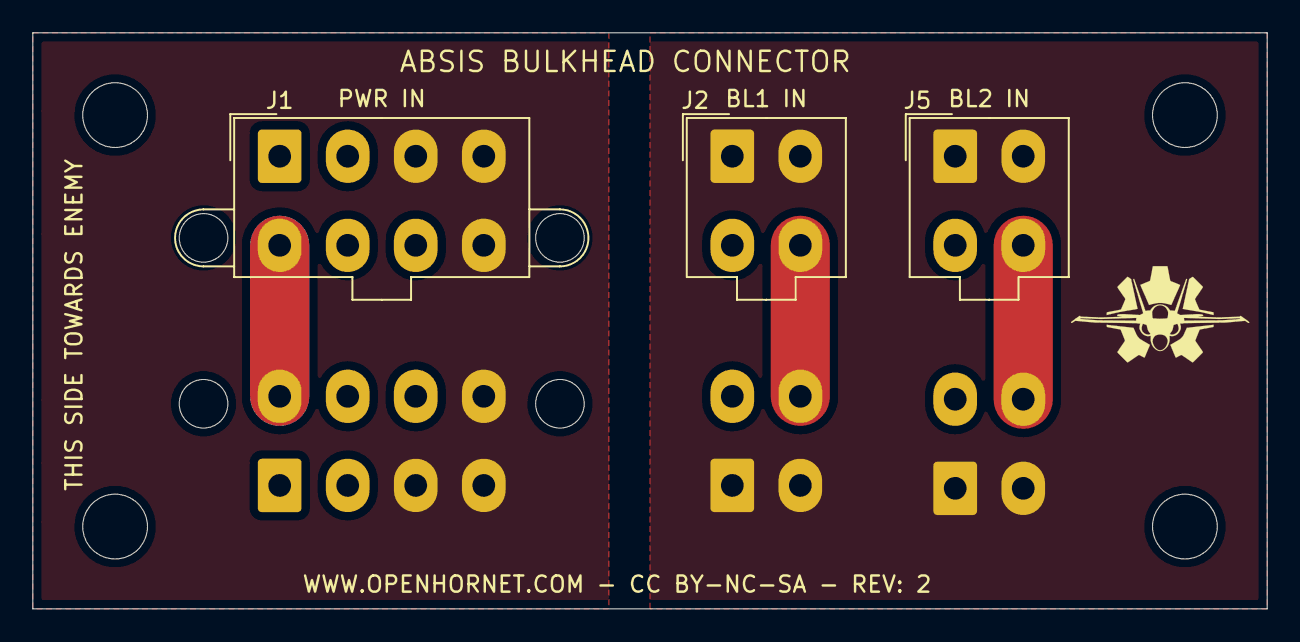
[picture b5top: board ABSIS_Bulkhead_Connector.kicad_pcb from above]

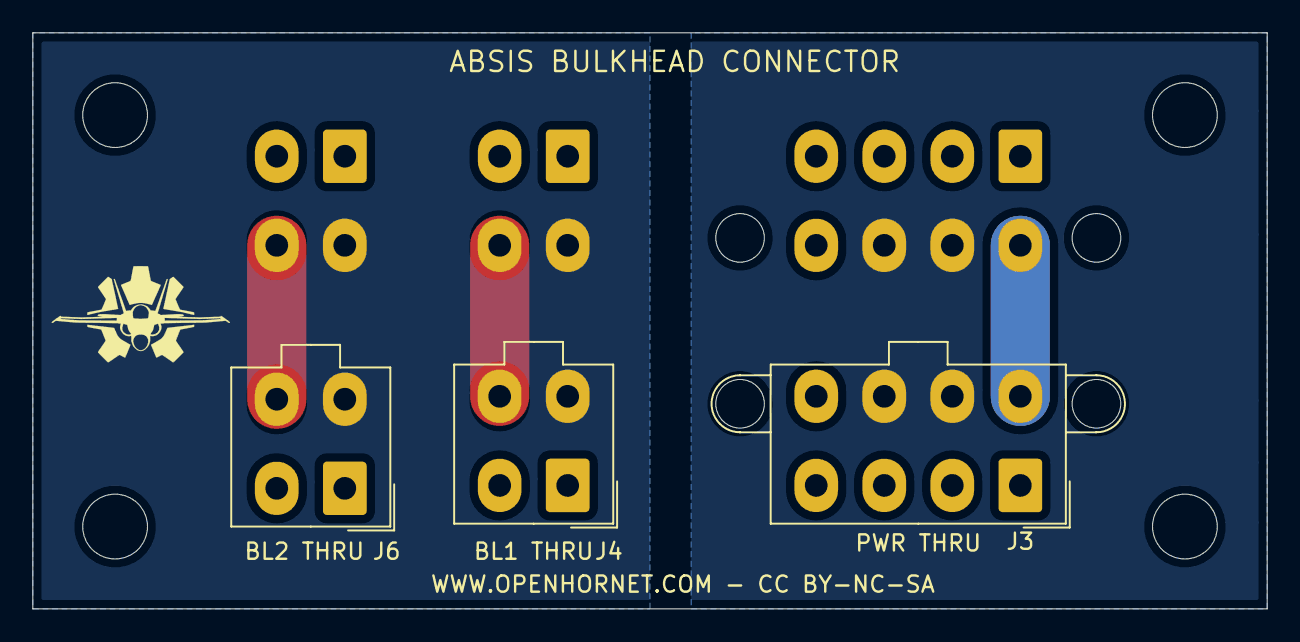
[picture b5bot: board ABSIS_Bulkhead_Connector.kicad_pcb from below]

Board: 4 copper layers, 76.2 x 35.6 mm, 10 parts (3 on the bottom side), 8 nets.

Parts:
H1, H2, H3, H4: MH; MountingHole_4mm
J1: PWR IN; Molex_Mini-Fit_Jr_5566-08A2_2x04_P4.20mm_Vertical
J2: BL1 IN; Molex_Mini-Fit_Jr_5566-04A_2x02_P4.20mm_Vertical
J3: PWR THRU; Molex_Mini-Fit_Jr_5566-08A2_2x04_P4.20mm_Vertical
J4: BL1 THRU; Molex_Mini-Fit_Jr_5566-04A_2x02_P4.20mm_Vertical
J5: BL2 IN; Molex_Mini-Fit_Jr_5566-04A_2x02_P4.20mm_Vertical
J6: BL2 THRU; Molex_Mini-Fit_Jr_5566-04A_2x02_P4.20mm_Vertical

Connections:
/ABSIS_+3.3V: J1.5, J3.5
/ABSIS_+5V: J1.6, J1.7, J3.6, J3.7
/ABSIS_+12V: J1.3, J1.4, J1.8, J3.3, J3.4, J3.8
/ABSIS_GND: J1.1, J1.2, J3.1, J3.2
/BL_+5V: J2.1, J2.2, J4.1, J4.2, J5.1, J5.2, J6.1, J6.2
/BL_DATA1: J2.4, J4.4
/BL_DATA2: J5.4, J6.4
/BL_GND: J2.3, J4.3, J5.3, J6.3

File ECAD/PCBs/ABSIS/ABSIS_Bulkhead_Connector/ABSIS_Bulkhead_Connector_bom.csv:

Comment,Designator,Footprint,LCSC
"MH","H1,H2,H3,H4","MountingHole:MountingHole_4mm",""
"PWR IN","J1","Connector_Molex:Molex_Mini-Fit_Jr_5566-08A2_2x04_P4.20mm_Vertical",""
"BL1 IN","J2","Connector_Molex:Molex_Mini-Fit_Jr_5566-04A_2x02_P4.20mm_Vertical",""
"PWR THRU","J3","Connector_Molex:Molex_Mini-Fit_Jr_5566-08A2_2x04_P4.20mm_Vertical",""
"BL1 THRU","J4","Connector_Molex:Molex_Mini-Fit_Jr_5566-04A_2x02_P4.20mm_Vertical",""
"BL2 IN","J5","Connector_Molex:Molex_Mini-Fit_Jr_5566-04A_2x02_P4.20mm_Vertical",""
"BL2 THRU","J6","Connector_Molex:Molex_Mini-Fit_Jr_5566-04A_2x02_P4.20mm_Vertical",""
"OpenHornetLogoSmall","LOGO1","OH_KiCAD_Libraries:OH_LOGO_37.7mm_5.9mm",""

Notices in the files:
ECAD/PCBs/ABSIS/ABSIS_AUX_Bulkhead_Connector/ABSIS_AUX_Bulkhead_Connector.kicad_pcb:
WWW.OPENHORNET.COM - CC BY-NC-SA
WWW.OPENHORNET.COM - CC BY-NC-SA - REV: 1
ECAD/PCBs/ABSIS/ABSIS_Bulkhead_Connector/ABSIS_Bulkhead_Connector.kicad_pcb:
WWW.OPENHORNET.COM - CC BY-NC-SA - REV: 2
ECAD/PCBs/ABSIS/ABSIS_Bus_Master/ABSIS_Bus_Master.kicad_sch:
License: CC BY-NC-SA
parts and their libraries:
https://creativecommons.org/licenses/by-nc-sa/4.0
